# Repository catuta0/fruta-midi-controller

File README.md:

# FrutaMIDI — fruit MIDI controller

A USB MIDI controller with 12 capacitive pads (expandable to 24), in the style of the Playtron: touch a piece of fruit, a plant or a glass of water and a note comes out. It uses a Raspberry Pi Pico and an MPR121 sensor, costs about 25 € and works on **Windows and Mac** without drivers.

The MPR121 detects the touch, the Pico turns it into MIDI notes and the computer makes the sound. To change sounds, just change programs: the hardware stays the same.

**Online sampler:** <https://catuta0.github.io/fruta-midi-controller/> (open it in Edge or Chrome)

**Two ways to build it:**
- **Breadboard:** no soldering. This README.
- **Single-sided PCB, version 1.3**, for etching at home with the chemical method, with KiCad schematic, BOM and assembly guide: [`hardware/`](hardware/).
  The board has one copper layer, on the component side, and every part is surface-mounted (SMD), so the only holes are the 4 optional M3 mounting holes. All parts are sold by Mouser; one board costs about 13.84 EUR at Mouser Portugal prices of 2026-11-11, excluding shipping and tax (a calculation from list prices). What to know before you start (details in the [assembly guide](hardware/README.md)):
  - The **Pico is soldered flat** on its castellations and the **MPR121 module stands on its header pins**, both soldered onto surface pads, with no sockets. Only the Pico (SC0915) and the Pico 2 are supported on the PCB, not Pico W or Pico 2 W; with a Pico 2, check that the USB plug seats fully before soldering it. Flash the firmware before soldering the Pico. Replacing a failed one means desoldering it, which is harder than with sockets.
  - **USB end:** two small beads of 2-part epoxy along the long sides of the Pico, over pins 1–3 and 38–40; none on the USB end face or beyond the board edge, and check again after curing that the plug seats fully. Use a strain-relieved USB cable and do not lever on the plug.
  - **Electrode wires** are soldered onto pads and held with hot-melt glue. The **octave potentiometer** sits off the board on 3 wires: use one with an insulated shaft and a plastic knob. It has no bushing; the guide suggests mounting it on a small piece of perfboard behind the panel hole (not tried).
  - Module configuration: **JP1** is a surface solder bridge (ORIG or QT), set **before the module is fitted** because the module hides the ORIG label, and **J1** takes two short wire links.
  - **ESD:** each electrode has a 3.3 kΩ chip resistor. It is **not proven** that these standard resistors survive the project's ±4 kV static-discharge target; nothing has been tested (see [Safety](#design-notes) below).

> The firmware compiles without errors for all the boards listed, and the sampler was tested with simulated MIDI. <!-- EVIDENCE --> The complete build has not yet been tested on real hardware: if you run into problems, open an *issue*.

## Contents

- [Quick start (no programming)](#quick-start-no-programming)
- [PCB version](hardware/) (separate page)
- [Bill of materials](#bill-of-materials)
- [Wiring](#wiring)
- [Firmware](#firmware)
- [Sound](#sound)
- [Windows: what to know](#windows-what-to-know)
- [Design notes](#design-notes)
- [Step-by-step assembly](#step-by-step-assembly)
- [Troubleshooting](#troubleshooting)

## Quick start (no programming)

Works on Windows 10/11 and macOS; you do not need to install anything.

1. Build the hardware: see [Wiring](#wiring).
2. On the [Releases](https://github.com/catuta0/fruta-midi-controller/releases/latest) page, download the file for your board:

   | Board | Breadboard | FrutaMIDI PCB |
   | --- | --- | --- |
   | Raspberry Pi Pico | `FrutaMIDI-rpipico.uf2` | `FrutaMIDI-pcb-rpipico.uf2` |
   | Raspberry Pi Pico W | `FrutaMIDI-rpipicow.uf2` | `FrutaMIDI-pcb-rpipicow.uf2` (not supported on the v1.3 PCB, see below) |
   | Raspberry Pi Pico 2 | `FrutaMIDI-rpipico2.uf2` | `FrutaMIDI-pcb-rpipico2.uf2` |
   | Raspberry Pi Pico 2 W | `FrutaMIDI-rpipico2w.uf2` | `FrutaMIDI-pcb-rpipico2w.uf2` (not supported on the v1.3 PCB, see below) |

   The PCB uses different pins from the breadboard, so each build has its own file.

   The v1.3 PCB supports only the Raspberry Pi Pico (SC0915, recommended) and the Pico 2. Pico W and Pico 2 W are not supported on the PCB until their undersides have been checked against the keep-outs under the Pico ([assembly guide, A1](hardware/README.md#bill-of-materials)). On the breadboard all four boards work.

3. Hold the Pico's **BOOTSEL** button while you plug in the USB cable. A drive called **RPI-RP2** (Pico 2: **RP2350**) appears in Windows File Explorer or the Mac Finder.
4. Drag the `.uf2` onto that drive. The Pico restarts by itself and the drive disappears: this is normal.
5. Open the [online sampler](https://catuta0.github.io/fruta-midi-controller/) in Edge or Chrome. Click to enable sound and allow MIDI access.
6. Touch the fruit.

## Bill of materials

The essentials cost about 23–31 €. This total excludes the 14 recommended resistors (and, on the PCB, the JP1 solder bridge), because their price is not sourced. Prices are approximate and vary a lot between shops.

| Part | Qty | Purpose | Approx. price | Notes |
| --- | --- | --- | --- | --- |
| Raspberry Pi Pico or Pico 2 (**H** version, with headers already soldered) | 1 | Brain; shows up on the computer as a MIDI device | 5–7 € | Pico W and Pico 2 W also work |
| MPR121 breakout (Adafruit 1982 or CJMCU-121 clone) | 1 | 12 capacitive sensors | 3 € (clone) / 9 € (Adafruit) | Both run at 3.3 V, like the Pico |
| Micro-USB **data** cable | 1 | Connection to the computer | 3 € | Many cables are charge-only; if the Pico does not show up, it is the cable |
| 400-point breadboard | 1 | Solderless prototype | 3 € | |
| Male-to-male jumper wires | 10 | Breadboard connections | 2 € | |
| Leads with alligator clips on both ends | 12 | Connect each pad to an object | 5 € (pack of 10) | Buy 2 packs |
| Screw terminal strip, 12 ways | 1 | Sturdy connection point for the alligator clips | 2 € | 5 mm pitch is the easiest to tighten |
| Resistor 3.3 kΩ (3k3), axial | 12 | One in series with each electrode (ESD protection) | — | Recommended. The PCB (v1.3) uses 3.3 kΩ ±1 % surface-mount chip resistors in the 2512 size (YAGEO RC2512FK-073K3L); see the [assembly guide](hardware/README.md#bill-of-materials) |
| Resistor 4.7 kΩ (4k7), axial | 2 | I²C pull-ups, SDA and SCL to 3V3 | — | Recommended, because the firmware runs I²C at 400 kHz (Yageo MFR-12FTF52-4K7) |
| 6 mm push button | 1 | Change scale / recalibrate | 0.20 € | Optional, but very useful |
| 10 kΩ linear potentiometer (B10K) + knob | 1 | Change octave | 1.50 € | Optional |
| Second MPR121 | 1 | Pads 13 to 24 | 3–9 € | Optional |
| Project box ~100×60×25 mm or 3D print | 1 | Protect the electronics | 5 € | Optional |
| Perfboard + soldering iron | 1 | Permanent version | 3 € | After testing on the breadboard |
| Stainless steel nails or needles, copper tape, conductive paint | — | Electrodes | 5–10 € | Optional |

The firmware also compiles for the Arduino Pro Micro / Leonardo (ATmega32u4). In that case, use an Adafruit MPR121 (it accepts 5 V) or a 3.3 V Pro Micro: MPR121 clones only tolerate 3.3 V.

## Wiring

| Pico (GP) | Physical pin | Connects to | Function |
| --- | --- | --- | --- |
| 3V3(OUT) | 36 | MPR121 **VIN** (Adafruit) or **3.3V** (clone) | Sensor power |
| GND | 38 | MPR121 **GND** | Common ground |
| GP4 | 6 | MPR121 **SDA** | I²C data |
| GP5 | 7 | MPR121 **SCL** | I²C clock |
| — | — | MPR121 **IRQ** | Not connected: the firmware polls the sensor in a loop |
| — | — | MPR121 **ADDR** | Leave as is (0x5A); only changes on the 2nd sensor |
| GP15 | 20 | Button, leg 1 | Scale / recalibrate; the other leg goes to GND (pin 18) |
| GP26 / ADC0 | 31 | Potentiometer, middle pin | Octave (optional) |
| 3V3(OUT) | 36 | Potentiometer, one end | |
| AGND | 33 | Potentiometer, other end | |
| 3V3(OUT) | 36 | 4.7 kΩ resistor to SDA (GP4), and another 4.7 kΩ to SCL (GP5) | I²C pull-ups (recommended) |
| — | — | MPR121 **0–11** | Each pin through its own 3.3 kΩ resistor to the terminal strip, then one alligator clip per object |

Physical pins are counted from 1 to 40 with the USB facing up: pin 1 is the top-left corner, you go down the left side to 20 and back up the right side to 40.

**Second MPR121 (24 pads).** Connect it in parallel with the first, on the same 3V3, GND, SDA and SCL. To change its address to 0x5B, connect its **ADDR** pin to 3V3. On the clone, ADDR usually comes tied to GND by a trace or solder bridge that you must cut first. In the firmware, set `NUM_SENSORS = 2`; the `.uf2` files in Releases are for 1 sensor. With `NUM_SENSORS = 2`, an LED that keeps blinking fast means one of the two modules is not answering.

**Pro Micro / Leonardo.** SDA = pin 2, SCL = pin 3, button on pin 7, potentiometer on A0.

**Protection and pull-ups (recommended).** Put a 3.3 kΩ resistor in series between each MPR121 electrode pin (0–11) and its terminal, so the resistor sits between the sensor and anything you touch. Add two 4.7 kΩ pull-ups from 3V3 to SDA and to SCL: the firmware runs I²C at 400 kHz. These are the same values used on the [PCB](hardware/README.md#electrical-safety).

Keep the I²C wires short (under 10 cm). The leads to the fruit can be 20–50 cm, but kept apart from each other.

## Firmware

The code is in [`firmware/FrutaMIDI/FrutaMIDI.ino`](firmware/FrutaMIDI/FrutaMIDI.ino), with helper headers `fm_*.h` in the same folder. The scales are defined in [`fm_scales.h`](firmware/FrutaMIDI/fm_scales.h). You only need to compile it if you want to change the configuration; otherwise, use the `.uf2` files from the [Quick start](#quick-start-no-programming).

**What it does**

- Each touched pad sends Note On; when you let go, it sends Note Off for the same note, even if you have changed scale in the meantime.
- While you touch, it sends Polyphonic Aftertouch (0–127): more skin, or the hand closer, gives a higher value. When you let go, it sends aftertouch 0 before the Note Off, so the pressure never stays stuck. After an octave change two pads can play the same note: it sounds until the last of them is released.
- It has 6 scales. It starts in Drum Rack mode (notes 36–47, for triggering samples); the others are melodic.
- Button: a short press moves to the next scale and the LED blinks its number (1 Drum Rack · 2 Major pentatonic · 3 Minor pentatonic · 4 Major · 5 Natural minor · 6 Chromatic). Held for 0.8 s, it recalibrates.
- LED: 2 slow blinks at startup = sensor OK; blinking fast = MPR121 not found or lost during play (its notes are released and it retries about every 2 s); on = pad touched. The pads keep playing while the LED blinks; while a blink pattern runs, the LED shows the pattern instead of touches.

**Compiling (Arduino IDE 2, same on Windows and Mac)**

1. In the Arduino IDE preferences (*File → Preferences* on Windows, *Arduino IDE → Settings* on Mac), add this address to *Additional boards manager URLs*:
   `https://github.com/earlephilhower/arduino-pico/releases/download/global/package_rp2040_index.json`
2. In the *Boards Manager*, install **Raspberry Pi Pico/RP2040/RP2350** (Earle F. Philhower).
3. In the *Library Manager*, install **Adafruit MPR121** (accept the dependencies) and **MIDI Library** (FortySevenEffects). For the Pro Micro, install **MIDIUSB** instead of the MIDI Library.
4. Under *Tools*: *Board* → your board; *USB Stack* → **Adafruit TinyUSB**. Without this step it does not compile.
5. First upload: hold **BOOTSEL** while you plug in the USB and click *Upload*. Later uploads are automatic (on Windows, the Pico shows up as a COM port).

**Configuration** (at the top of the file)

| Constant | Default | Purpose |
| --- | --- | --- |
| `NUM_SENSORS` | 1 | 2 for 24 pads |
| `MIDI_CHANNEL` | 1 | MIDI channel (1–16) |
| `VELOCITY` | 100 | Fixed note velocity |
| `TOUCH_THRESHOLD` / `RELEASE_THRESHOLD` | 12 / 6 | Sensitivity: higher = less sensitive |
| `AUTOCONFIG` | true | Adjusts the charge current to the size of each object. Leave it on for fruit |
| `SEND_AFTERTOUCH` | true | Sends the "pressure" as Polyphonic Aftertouch |
| `USE_BUTTON` / `USE_POT` | true / false | Enables the button and the potentiometer |
| `SERIAL_DEBUG` | false | Prints each pad's "delta" to the Serial Monitor (115200) |
| `#define FRUTAMIDI_PCB` | off | Uncomment for the [PCB](hardware/): I²C on GP26/GP27, button on GP22, potentiometer on GP28 (and enabled) |

**Tuning the sensitivity:** set `SERIAL_DEBUG = true`, upload the firmware again and open the Serial Monitor. You see each pad's delta 4 times per second: close to 0 at rest, rising when you touch. `TOUCH_THRESHOLD` should sit roughly in the middle.

## Sound

FrutaMIDI does not make sound: it sends notes. Choose a program to turn them into sound.

**Browser sampler (included).** Open <https://catuta0.github.io/fruta-midi-controller/> in **Edge** (it comes with Windows) or Chrome. Safari does not have Web MIDI. The file is at [`docs/index.html`](docs/index.html) and also works when downloaded.

- 12 pads with synthesised drum sounds, mapped to notes 36–47 (the firmware's Drum Rack mode).
- Drag a wav, mp3 or ogg onto a pad to replace its sound.
- The **"learn"** button changes a pad's note: click it and touch the fruit.
- Notes without a pad (melodic scales) play on a synthesiser, and aftertouch opens the filter.
- Without hardware, the keys 1–4 / Q–R / A–F play the pads.

**Music programs**

| Program | System | Cost | How to use |
| --- | --- | --- | --- |
| [LMMS](https://lmms.io) | Windows, Mac, Linux | Free | *AudioFileProcessor* or *Kicker* instrument; enable MIDI input on the track |
| [Ableton Live](https://www.ableton.com/live/) | Windows, Mac | Paid, with trial version | Drum Rack (C1–B1 = notes 36–47); *Settings → Link, Tempo & MIDI* → enable **Track** on the FrutaMIDI input |
| [FL Studio](https://www.image-line.com) | Windows, Mac | Paid, with trial version | *FPC* for pads; enable FrutaMIDI in *Options → MIDI settings* |
| [Reaper](https://www.reaper.fm) | Windows, Mac | Free trial, cheap licence | Track with *ReaSamplOmatic5000*; MIDI record input → FrutaMIDI |
| GarageBand | Mac only | Free | *Software Instrument* track; recognises FrutaMIDI by itself |

For the classic "Playtron" effect (the sound lasts while your hand is on the fruit), use the DAW's sampler in *gate* or *hold* mode, not *one-shot*.

## Windows: what to know

- **No drivers.** Windows 10 and 11 recognise FrutaMIDI by themselves. To check, open *Device Manager*: it appears under *Sound, video and game controllers*.
- **One program at a time.** On Windows, a MIDI device can normally be opened by only one program at a time. If the DAW says FrutaMIDI is unavailable, close the sampler tab in the browser (and vice versa). The sampler warns you when the device is busy. The most recent versions of Windows 11 include *Windows MIDI Services*, which may lift this limitation.
- **Latency.** In the DAW, use an **ASIO** driver: your sound card's or, on a laptop without one, the free [ASIO4ALL](https://asio4all.org) or [FlexASIO](https://github.com/dechamps/FlexASIO). Set the buffer to 128 or 256 samples. With the standard driver (MME/shared WASAPI) the delay is noticeable.
- **Device name.** Windows keeps the name of the first device it saw with that USB identifier. If you have used the Pico with other firmware before, it may show up under another name; it works all the same.
- **Laptop on battery.** As on the Mac, sensitivity drops when the laptop is not plugged into the charger (see [Design notes](#design-notes)).

## Design notes

What matters most for the result is not the code: it is the objects, the cables and the ground connection. The MPR121 measures the capacitance of each electrode. When you touch it, your body, grounded through the floor and the computer, adds capacitance and the reading drops. The "delta" is that drop.

**Ground and computer**

- The circuit closes through you and the computer. A laptop on battery gives smaller, unstable deltas; plugged into the charger it usually improves.
- Makey Makey trick: an alligator clip connected to the Pico's GND on a wristband or on a "ground" object. Anyone touching it with the other hand gets a much stronger and more consistent touch.

**Which objects work**

- Good: fruit and vegetables with water in them (lemon, apple, cucumber, potato), thick-leaved plants, water in a glass, metal, copper tape, conductive paint, heavily shaded 6B pencil drawings, homemade salt dough.
- Bad: dry wood, plastic, glass, very dry fruit or fruit with a thick, dry skin.
- Objects must not touch each other or sit on a wet surface: that shorts pads together.
- For long events, hard vegetables (potato, carrot, apple) last for days; bananas and strawberries spoil quickly.

**Connecting to the object**

- An alligator clip on the skin alone works poorly. Push in a stainless steel nail or needle, or 1–2 cm of stripped wire, and clip onto that.
- Fruit acid oxidises copper within a few hours. Stainless steel lasts much longer.

**Cables**

- The cable itself is part of the electrode: touching the wire also triggers the note, and long cables pick up noise.
- Use up to 50 cm per cable, kept apart from each other. Do not use flat multi-conductor cable or tied bundles: touching one wire triggers its neighbour (crosstalk).

**Calibration and sensitivity**

- At startup, the MPR121 measures each electrode's "baseline" and, with `AUTOCONFIG`, adjusts the charge current to the size of the object. Connect the fruit before the USB, or hold the button for 0.8 s after swapping objects, without touching anything.
- Ghost notes: raise the thresholds to 20 / 10. No response: lower them to 8 / 4. Measure first with `SERIAL_DEBUG`.
- Very large objects (a whole watermelon, a pot of damp soil) can fall outside the sensor's range: the pad stays on all the time or never turns on. Use a smaller object or a piece of it.

**Enclosure and permanent version**

- After testing on the breadboard, solder everything onto a perfboard. Put the Pico in a female header so you can remove it.
- Terminal strip or 4 mm binding posts on the lid, numbered 0–11, and holes for the USB and the button.
- Use a plastic or wooden box: metal near the electrodes takes away sensitivity.

**Safety.** FrutaMIDI is USB-powered with 3.3 V logic. On the [PCB (v1.3)](hardware/README.md#electrical-safety), each electrode has a 3.3 kΩ series chip resistor (2512 size) and sits next to a spark gap to GND. The protection target is an IEC 61000-4-2 contact discharge of ±4 kV, and that target is itself an assumption. Whether the resistors survive it is **not proven**: they are standard parts with no published surge rating, a choice accepted to keep the board cheap. If the planned physical ESD test shows damage (a resistor whose value shifts, a channel that stops detecting touch, or a spark across a resistor), the fallback is a board revision with clamp diodes. Nothing has been tested, and the board does not cover 8 kV. The PCB has not been evaluated beyond that. Use an insulated-shaft potentiometer with a plastic knob on the PCB: a metal shaft is not protected. The breadboard build has no ESD protection on the electrodes beyond the MPR121's internal protection (HBM ±2 kV): the module connects its electrode pins straight to its header. The recommended 3.3 kΩ series resistors (see [Wiring](#wiring)) have the same value as the PCB's protection, but a small resistor is not rated for the ESD pulse, and no resistor has been evaluated in a breadboard layout. Neither build has been evaluated for touching while connected to mains-powered equipment. <!-- EVIDENCE --> Never connect the electrodes to anything plugged into mains power.

## Step-by-step assembly

Test each step before moving on: when something fails, you know straight away where the problem is.

1. **Pico alone.** Upload the firmware with only the Pico connected. The LED should blink fast, because there is no sensor yet, and FrutaMIDI already shows up in the sampler.
2. **Sensor.** With the USB unplugged, place the Pico and the MPR121 on the breadboard and connect the 4 wires: 3V3, GND, SDA and SCL, plus the two 4.7 kΩ pull-ups (3V3 to SDA, 3V3 to SCL). When you plug in the USB: 2 slow blinks, then the LED off.
3. **First touch.** Touch pin 0 of the MPR121 directly with your finger. The LED lights up and the sampler shows "Note On C1 (36)".
4. **First fruit.** One alligator lead from pin 0 to a nail pushed into a lemon. Recalibrate (0.8 s on the button, or unplug and replug the USB) without touching anything, then touch the lemon.
5. **Tune.** If there are ghost notes or missed touches, adjust the thresholds (see [Design notes](#design-notes)).
6. **All 12 pads.** Add the terminal strip, with a 3.3 kΩ resistor between each MPR121 pin and its terminal, and the rest of the fruit, recalibrate, and test pad by pad in the sampler.
7. **Controls.** Add the button (GP15 ↔ GND) and, if you like, the potentiometer with `USE_POT = true`.
8. **Final version.** Move to the perfboard and the enclosure.

## Troubleshooting

| Symptom | Likely cause | What to do |
| --- | --- | --- |
| Compile error mentioning `Adafruit_TinyUSB` or `usbMidi` | Wrong USB Stack | *Tools → USB Stack → Adafruit TinyUSB* |
| The Pico does not show up at all | Charge-only cable | Change the cable; test with BOOTSEL held (the RPI-RP2 drive should appear) |
| LED keeps blinking fast | MPR121 not responding on I²C | Check 3V3/GND and that SDA→GP4 and SCL→GP5 are not swapped; on the 2nd sensor, check ADDR |
| Windows: the DAW does not see FrutaMIDI, or the sampler says "ocupado" (busy) | Another program has the device open | Close the other program (or the sampler tab) and reopen |
| It shows up, but the DAW does not play | MIDI input disabled or track not armed | Enable the FrutaMIDI input in the DAW's MIDI settings and arm the track |
| Windows: the sound arrives late | Audio driver without ASIO | Use ASIO (ASIO4ALL or FlexASIO) with a buffer of 128–256 |
| A pad is always on | It calibrated with a hand on the object, or the object is too large | Recalibrate without touching; use a smaller object; raise the threshold |
| Touching one pad triggers its neighbour | Wires together or objects touching | Move the cables apart and separate the objects; dry the table |
| Ghost notes when the hand gets close | Low threshold or long cables | Raise to 20 / 10; shorten the cables |
| Sensitivity changes over the day | Fruit drying out, laptop on battery | Recalibrate; plug in the charger; use the ground-wire trick |
| A note gets stuck in the DAW | You unplugged the USB with a hand on the object | Touch and release the same pad again: the Note Off frees the note |
| The sampler says there is no Web MIDI | Safari, or an old browser | Use Edge or Chrome |

## Licence

[MIT](LICENSE): you are free to use, modify and share it.

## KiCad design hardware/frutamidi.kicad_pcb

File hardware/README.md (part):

# FrutaMIDI: single-sided SMD PCB (version 1.3)

A 100 × 70 mm board with copper on the **component side only**, designed for chemical etching at home (toner transfer or photosensitive board). Everything is surface-mounted, so the only holes are the 4 M3 mounting holes. The board carries a Raspberry Pi Pico soldered on its castellations, an Adafruit MPR121 module (1982) standing on its header pins, 14 solder-wire pads for the electrodes and GND, a button, three wire pads for an off-board potentiometer, a 3.3 kΩ series resistor on each electrode, two I²C pull-up resistors and two 220 Ω I²C series resistors.

> **Status:** the schematic passes ERC and the PCB passes DRC, both with no violations, and the PCB matches the schematic. <!-- EVIDENCE --> The board has not been fabricated, soldered or tested. Hand-soldering the Pico and the module header joints has not been tried. ERC and DRC passing does not validate the hardware. If you make one, open an *issue* with the result.

## Contents

- [Files](#files)
- [Bill of materials](#bill-of-materials)
- [Design rules for home etching](#design-rules-for-home-etching)
- [1. Print](#1-print)
- [2. Transfer and etch](#2-transfer-and-etch)
- [3. Drill](#3-drill)
- [4. Solder](#4-solder)
- [5. Module configuration: JP1 and two wires](#5-module-configuration-jp1-and-two-wires)
- [6. Test before soldering the Pico and the module](#6-test-before-soldering-the-pico-and-the-module)
- [7. Firmware and first power-up](#7-firmware-and-first-power-up)
- [Common problems](#common-problems)
- [Electrical safety](#electrical-safety)
- [Modifying the board](#modifying-the-board)

## Files

| File | Purpose |
| --- | --- |
| [`fabrication/1-copper-for-transfer.pdf`](fabrication/1-copper-for-transfer.pdf) | **What you print** for toner or positive photosensitive board. 1:1 scale, already mirrored for transfer onto the component-side copper |
| [`fabrication/1b-copper-negative.pdf`](fabrication/1b-copper-negative.pdf) | The same in negative, only for dry film / negative resist |
| [`fabrication/2-assembly-map.pdf`](fabrication/2-assembly-map.pdf) | Where each component goes, with references and pin 1. There is no silkscreen on the board: keep this page at the bench |
| [`fabrication/frutamidi-schematic.pdf`](fabrication/frutamidi-schematic.pdf) | Schematic |
| [`fabrication/gerbers/`](fabrication/gerbers/) | Gerbers + Excellon drill files, if you prefer to order the board |
| [`fabrication/bom-kicad.csv`](fabrication/bom-kicad.csv) | BOM exported from KiCad, with manufacturer, part number and Mouser number columns |
| `frutamidi.kicad_pro` / `.kicad_sch` / `.kicad_pcb` | KiCad 10 project, with its own libraries (`FrutaMIDI.kicad_sym`, `FrutaMIDI.pretty/`) |
| [`scripts/`](scripts/) | Schematic and PCB generators, and `build_all.sh` (regenerates, checks and exports) |

## Bill of materials

### Components

All parts below are sold by Mouser. One board costs about 13.84 EUR at Mouser Portugal prices of 2026-11-11 (12 resistors at the 10+ price, everything else at the single-unit price), excluding shipping and tax.

| Ref. | Part | Qty | Notes |
| --- | --- | --- | --- |
| A1 | Raspberry Pi Pico, Raspberry Pi **SC0915** (Mouser 358-SC0915). The **Pico 2** also fits. **Pico W and Pico 2 W are not supported on this board** until their underside has been checked against the keep-outs. The castellated pads must be free, so **no** H version with headers fitted | 1 | Surface-soldered on its castellated edge pads. There are no sockets: a failed Pico must be desoldered from the surface. The keep-outs under it cover the test points and USB pads of both the Pico and the Pico 2, including the Pico 2's TP7 (1.1 V core supply) |
| A2 | Adafruit MPR121 12-key capacitive touch breakout, Adafruit **1982** (Mouser 485-1982) | 1 | Original or STEMMA QT: both work (section 5). Use the male headers supplied with it |
| R1–R12 | Thick-film chip resistor 3.3 kΩ ±1 %, 1 W, 2512, YAGEO **RC2512FK-073K3L** (Mouser 603-RC2512FK-073K3L) | 12 | One in series with each electrode. **Stock is tight:** Mouser showed 13 in stock on 2026-11-11, next delivery May 2027. Any 3.3 kΩ ±1 % 2512 chip with a body 6.35 × 3.1 mm fits the same pads. **Alternative in stock:** Vishay **CRCW25123K30FKEG** (Mouser 71-CRCW25123K30FKEG, 3.3 kΩ 1 %, 2512): Mouser showed 4,500 in stock on 2026-11-11, 0.424 EUR each at 10+ (about 5.09 EUR for 12, against 1.31 EUR for the YAGEO part). Its datasheet has not been checked for this board: confirm that the body is the standard 6.35 × 3.1 mm 2512 size before ordering. Neither part has a published surge rating, see [Electrical safety](#electrical-safety) |
| R13, R14 | Resistor 4.7 kΩ 1 %, 1206, YAGEO **RC1206FR-074K7L** (Mouser 603-RC1206FR-074K7L) | 2 | I²C pull-ups (SCL, SDA) |
| R15, R16 | Resistor 220 Ω 1 %, 1206, YAGEO **RC1206FR-07220RL** (Mouser 603-RC1206FR-07220RL) | 2 | In series in SCL (R15) and SDA (R16), on the Pico side; they limit the current if a configuration wire goes to the wrong pad |
| C1 | Ceramic capacitor 100 nF 50 V X7R, 1206, Samsung **CL31B104KBCNNNC** (Mouser 187-CL31B104KBCNNNC) | 1 | Potentiometer wiper to AGND, near the Pico |
| SW1 | Tactile switch **B3S-1000** (6 × 6 mm, SMD, height 4.3 mm; Mouser 653-B3S-1000) | 1 | Mouser lists the maker as **Aratas**; its maker page says "ARATAS, formerly Omron Components", so this is the genuine Omron B3S-1000 (checked 2026-11-11) |
| RV1 | 10 kΩ linear potentiometer, Bourns **PTV09A-4015F-B103** (Mouser 652-PTV09A-4015FB103; 9 mm, insulated flatted shaft 6 mm, 15 mm long, no bushing, PC pins), off-board, connected by 3 wires | 1 | Mount it in your enclosure and solder the 3 wires to its pins. See [Electrical safety](#electrical-safety): keep the insulated shaft and use a plastic knob. If the octave goes down when you turn clockwise, swap the two outer wires |
| — | Knob for RV1, Same Sky **SPK-016A** (Mouser 179-SPK-016A; ABS, 11 mm, for 6 mm shafts) | 1 | Whether its bore grips the flatted shaft is not confirmed; check the fit, or use any plastic knob for a 6 mm flatted (D) shaft |
| J1, J2, J3, JP1 | Etched copper pads only (no part): J1 configuration-wire pads, J2 electrode wire pads, J3 S1–S7 pads, JP1 solder bridge | — | Not in `bom-kicad.csv`. JP1 is bridged with a short tinned wire off-cut, see section 5. The RV1 knob is also not in `bom-kicad.csv` (it has no schematic symbol); this table is the full list |
| — | Thin insulated solid wire (from network cable, for example) | ~10 cm | The 2 configuration wires (SDA, SCL) |
| — | Electrode wire, insulated, 0.25–0.5 mm² | 12 + GND | Soldered to the J2 pads, then strain-relieved with hot-melt glue |
| — | Hot-melt glue, 2-part epoxy | — | Hot-melt on each J2 wire and RV1 wire; epoxy at the Pico USB end |
| H1–H4 | M3 screws + spacers, **nylon** preferred | 4 | Optional; see the mounting note in section 4. Nylon keeps loose metal away from the electrode resistors |
| — | Micro-USB **data** cable, strain-relieved or supported | 1 | The USB connector is held only by the castellation solder joints and the epoxy bead. Do not lever on the plug |

### Fabrication materials

| Part | Qty | Notes |
| --- | --- | --- |
| **Single-sided** copper board, FR4 or FR2, 100 × 70 mm (35 µm) | 1 | Or cut from a larger one |
| **Toner:** laser printer + transfer paper (or glossy magazine paper) + clothes iron | — | Inkjet ink does not work |
| **Photographic:** positive pre-sensitised board + transparency film + UV lamp + developer (sodium hydroxide) | — | Alternative to toner |
| Ferric chloride (or sodium persulfate) | ~0.5 L | See the safety note in section 2 |
| Plastic container, nitrile gloves, goggles | — | Nothing metal |
| Acetone or thinner, fine steel wool, isopropyl alcohol | — | Cleaning |
| Fine permanent marker | 1 | Touching up toner gaps |
| Drill bit of **3.2 mm** | 1 | For the 4 mounting holes, which are the only holes on the board |
| Soldering iron with a fine chisel tip, flux, flux-core solder (0.5–0.8 mm), tweezers, multimeter, polyimide tape (optional) | — | |

## Design rules for home etching

| Rule | Value |
| --- | --- |
| Copper layers | One layer, on the component side (top). SMD only |
| Holes | Only the 4 M3 mounting holes (not plated) |
| Track width | 1.0 mm (signals) and 1.2 mm (GND, 3V3); 0.8 mm on the short S-row stubs |
| Minimum clearance | 0.6 mm (project rule); 0.5 mm is the absolute minimum accepted by DRC |
| Vias and bridges | No vias, no copper pour. Only the JP1 solder bridge and the 2 module configuration wires |
| Pads | Pico 1.6 × 4.2 mm (all 40 etched, 0.94 mm gap), module 1.8 × 4.2 mm (13-pin row) and 1.8 × 5.5 mm (7-pin row, joined to the S1–S7 pads), 0.74 mm gap, J2 3.0 × 4.5 mm, RV1 3.0 mm, JP1 1.94 × 2.4 mm on a 3.81 mm pitch (1.87 mm between pads), 1206 parts 1.8 × 1.8–1.9 mm. Every hand-soldered pad reaches at least 1.0 mm beyond the part body (or the module outline), so the iron touches the pad outside the part |
| Keep-out under the Pico | No bare copper under the Pico's exposed test points and USB shell pads, nor under its 3 SWD pads: TP6 is BOOTSEL, so a short there means a Pico that always boots to mass storage |
| Ground plane | None, on purpose: copper around the electrode tracks takes away sensitivity |

## 1. Print

1. Open [`1-copper-for-transfer.pdf`](fabrication/1-copper-for-transfer.pdf) and print at **actual size / 100 %**, without "fit to page".
2. Measure the printed outline: it must be **100 × 70 mm**. If it is not, the printer scale is wrong.
3. Check that the text **"FrutaMIDI v1.3" appears reversed (mirrored) on the paper**, and that the Pico pads appear on the **right** of the page. That is intended: transferred onto the copper, the text reads correctly when you look at the copper with the components on it.
4. For toner: laser printer, maximum density, transfer paper. For photosensitive board: transparency film, preferably two copies stacked so it is fully opaque.

## 2. Transfer and etch

**Preparing the board:** cut the blank **oversize**, about 110 × 80 mm, and rub the copper with steel wool until it shines. The outline is printed with the tracks and etched as a thin copper line: after etching (and before soldering), trim the board to the **outside of that etched line** with a saw or shears and file the edges. The Pico's USB end lies on the top edge, with its connector sticking out about 1.2 mm, so do not cut inside the line at that edge. Clean it with alcohol and do not touch it with your fingers again.

**Toner**

1. Place the paper with the ink facing the copper and hold it with tape.
2. Iron on maximum, no steam, 3–5 minutes with pressure, going well over the corners.
3. Let it cool, soak in warm water for 5–10 minutes and remove the paper by rubbing with your finger.
4. Touch up broken tracks or pads with holes using the permanent marker.

**Positive photosensitive**

1. Place the transparency with the ink facing the resist.
2. Expose to UV light as the manufacturer specifies (usually 1–3 minutes), develop, rinse in water and check that the tracks are sharp.

**Etching**

- Ferric chloride at 40–50 °C (water bath), agitating: 10–20 minutes. Take the board out when all the copper between the tracks has gone.
- Rinse with water, remove the toner/resist with acetone, and check against the light that there are no bridges between tracks, especially between the Pico pads, in the electrode fan-out and at JP1.
- **Keep the 1.4 mm gap between each electrode pad and the GND track along the bottom edge clean and open:** it is an intentional spark gap (see [Electrical safety](#electrical-safety)).

**Safety:** wear gloves and goggles, in a ventilated place. Ferric chloride stains everything permanently and is corrosive. Do not pour the used solution down the drain: it contains dissolved copper, so take it to a recycling/waste collection centre. If you use hydrochloric acid with hydrogen peroxide, always mix it in small quantities and outdoors, because it releases toxic gases.

## 3. Drill

Drill only the 4 mounting holes, **3.2 mm**, at H1–H4 (see the assembly map). They are optional: without them the board can be fixed with adhesive feet. There are no other holes.

If you like, tin the bare copper with the iron or apply protective lacquer after etching, but keep lacquer off every pad you are going to solder.

## 4. Solder

Use the [assembly map](fabrication/2-assembly-map.pdf). Work from the lowest parts to the tallest. **Clean flux from around R1–R12 afterwards with isopropyl alcohol:** residue on the bare FR-4 between the two ends of each resistor shortens the surface path that the 4 kV estimate relies on.

1. **R13–R16 (1206) and C1 (1206).** Tin one pad, place the part with tweezers, solder that end, then the other. C1 is not polarised.
2. **R1–R12 (2512, 3.3 kΩ).** One per electrode, in one row between the module and J2. Keep solder off the 5.0 mm gap between the two pads and do not let any wire or solder cross it.
3. **Button SW1** (B3S-1000). Align all four legs on their pads and solder them all.
4. **[Run section 6 now](#6-test-before-soldering-the-pico-and-the-module)**, before the Pico and the module go on. After that you cannot get under them.
5. **Pico (A1).** Flash the firmware first, while the Pico is still loose (section 7). Check that no bare copper shows under the test-point areas marked on the assembly map. Lay the Pico on its pads with the USB end at the top edge of the board: the end of the Pico is 0.1 mm inside the board edge and the USB connector sticks out about 1.2 mm beyond it. **Before soldering, plug the cable in** with the Pico held in place: the plug must go fully home without touching the board edge; if it does not, file the board edge back to the etched outline. Press the Pico down at each corner: it must **not rock**. Solder left at the USB connector pins on the Pico's underside can hold it up; if it rocks, remove that solder with braid first. Then align the castellations over the pads, hold the board flat, tack two opposite corner pads, check alignment, then solder all 40 pads from the outer edge of each castellation. All 40 are anchors, even those without a track.
6. **Epoxy at the USB end.** After soldering and after a first USB check that the Pico still starts (the fast LED blink without the module is expected), apply a small bead of 2-part epoxy along the end of the Pico at the USB connector, joining the module edge to the board, without touching the USB opening. Use a strain-relieved cable: a sharp pull on the plug can peel the end pads.
7. **Module (A2).** Fit the supplied male header to the module from below, short pins up through the module, with the plastic strip pushed **up against the underside** of the module, and solder the pins on the top of the module. Cut the long pins below the strip to **3.0 mm** (measure from the strip; cut all 20 to the same length, a strip of card 3 mm thick helps). Stand the module on its 20 pads (13-pin row towards J2, as on the assembly map): each pin stands near the inner end of its pad, and the pad runs about 1.7 mm out beyond the edge of the module. Solder each pin from **outside the module**: put the iron on the outer part of the pad, feed solder where the pad meets the pin, and check that a fillet climbs the pin. The module must sit level on both rows; tack one pin at each end of each row first. The underside of the module ends up about 5.5 mm above the board (3.0 mm pin + 2.5 mm strip, not measured), which keeps its copper and vias well off the bare tracks; the top of the module board is about 7.1 mm above the copper, plus the parts on it (the 1.6 mm module thickness is assumed, not measured).
8. **JP1 and the 2 configuration wires** (section 5).
9. **RV1 wires.** Three insulated wires to pads 1 (3V3), 2 (wiper), 3 (AGND) to your off-board pot. Add a small bead of hot-melt over the wires, on the pads, for strain relief. Keep the wires short.
10. **Electrode and GND wires (J2).** Strip about **3–4 mm** of each wire and tin it. Lay it on the upper half of its pad so that the wire leaves the pad **upwards, towards the resistors, away from the board edge**, and solder it there, leaving the part of the pad next to the board edge clean. A wire led out over the bottom edge would cross the spark gap: lead the wires sideways off the board only after the hot-melt, above the pads. Add a bead of hot-melt over the wire and the upper pad. **Keep the glue away from the 1.4 mm gap at the bottom of the pad:** the spark gap must stay open air.

**Optional: silicone over R1–R12.** It is not needed to meet the 3.5 mm gap rule, which the resistor terminations already meet. If you want an extra cover against dust and moisture, apply it only after cleaning and after the tests in section 6, as one continuous bead without bubbles or voids over each resistor and its two pads. Use only a **neutral-cure, electronics-grade** silicone, never an acetic-cure (vinegar-smelling) bathroom silicone, which corrodes copper and solder. No particular product has been checked for this board.

**Mounting (M3).** The four holes are at H1 (5.0, 65.0), H2 (96.0, 4.0), H3 (96.5, 58.0) and H4 (29.8, 4.0) mm from the top-left board corner, as seen on the assembly map; the outer circle drawn around each hole is the 7 mm area kept free of copper. H4 is the screw closest to the USB end of the Pico: fit it if you fit any, because it stops the board bending when a cable is pulled. It does not make the Pico solder joints stronger, so the epoxy bead and a strain-relieved cable stay necessary.

Use M3 screws no wider than 5.6 mm under the head, with a washer of at most 7 mm. **Nylon screw and nylon washer preferred**, above all at H3, which is nearest the electrode resistors (and at H4, where a 7 mm metal washer would be only 0.6 mm from the Pico pads and the 3V3 track). If you use metal hardware, check after tightening that no washer touches copper or a part.

**Rework:** the Pico and the module are soldered flat, so a failed one has to be desoldered from the surface. Use plenty of flux and hot air or a wide iron tip on one side at a time.

## 5. Module configuration: JP1 and two wires

The Adafruit 1982 exists in two versions, with the 7 power/I²C pins in a different order. That is why the board does not connect them directly. Above the 7 module pins there are 7 surface pads **S1–S7** (J3), each one directly above a module pin. You configure the board for your module in two steps.

**Step 1: power (JP1).** JP1 is a 3-pad solder bridge standing upright to the right of the module, with **QT** etched above its top pad (pad 3) and **ORIG** etched to its left, beside the gap between the centre pad and the bottom pad. ORIG means the bottom pad (pad 1), where the S1 track comes in from the left; QT means the top pad (pad 3), where the S7 track comes in. The centre pad is 3V3. Bridge it to **one** side with a short tinned wire off-cut soldered flat across the two pads, or with solder. The pads are 3.81 mm apart (1.87 mm of bare board between them), so that a single blob cannot easily join all three; a solder-only bridge needs generous solder, the wire off-cut is easier:

- **ORIG** (pad 1 → S1): original version, 3V3 goes to **VIN**.
- **QT** (pad 3 → S7): STEMMA QT version, 3V3 goes to **VCC**.

**Step 2: I²C (two wires).** J1 (right of JP1) has 2 surface pads, **SCL on the left and SDA on the right**. Connect:

- J1 **SDA** → the S pad above the module's **SDA** pin;
- J1 **SCL** → the S pad above the module's **SCL** pin.

To confirm, read the letters printed on the module next to the 7-pin row, and check this table:

| Version | How to recognise it | JP1 | SDA → | SCL → |
| --- | --- | --- | --- | --- |
| Original | No small white connectors | **ORIG** | **S5** | **S6** |
| STEMMA QT (current) | Two small white 4-pin connectors (STEMMA QT / Qwiic) | **QT** | **S3** | **S4** |

Use insulated solid wire, run flat on the board and as short as the route allows (about 25–35 mm each). Solder each end flat on its surface pad, then add a small dab of hot-melt so the wire is not held by the joint alone. The module's GND needs no wire: it comes in through the electrode row and is the same in both versions.

> **A wrong JP1 position can damage the sensor.** ORIG on a STEMMA QT module puts 3V3 on the module's ADDR pin; QT on an original module puts it on IRQ. The MPR121 chip is then unpowered, so 3V3 on that pin is above its absolute maximum rating (VDD + 0.3 V), and it can back-feed the module through its 10 kΩ pull-ups. There is no direct short to GND, but the module is not supplied correctly, the sensor does not respond and the Pico LED blinks fast. Check JP1 against the table above **before** powering. Never bridge all three pads.

## 6. Test before soldering the Pico and the module

With the multimeter, after step 3 of section 4 and **before the Pico and the module go on**, because you cannot reach underneath them afterwards:

- [ ] Continuity between the **JP1 centre pad** (3V3) and a **GND** pad of J2: it must **not** beep.
- [ ] Resistance between each electrode pad of J2 and the matching pin pad of the 1×13 module row: about **3.3 kΩ** (3267–3333 Ω, plus your meter's error). It does not beep in continuity mode.
- [ ] Continuity between neighbouring J2 pads (0–1, 1–2, …): it does **not** beep.
- [ ] Continuity between the two GND pads at the ends of J2: it beeps.
- [ ] Resistance between the pads of pin 31 and pin 32 of the Pico footprint and the J1 SDA / SCL pads (through R16 / R15): about **220 Ω**.
- [ ] Inspect with a magnifier: no bridges between the Pico pads, no copper left in the keep-out areas marked on the assembly map.

Then the final checks, after the Pico and module are soldered and JP1 is bridged, with the USB still unplugged:

- [ ] Continuity between the JP1 centre pad and the S pad for your version (S1 for ORIG, S7 for QT): it beeps. The other side (S7 or S1) must **not** beep.
- [ ] Pico pads **36** (3V3), **39** (VSYS) and **40** (VBUS) to any GND pad (for example Pico pad 38): none of them may beep. Pads 39 and 40 have no track on this board but lie 0.94 mm from the GND pad 38, so a solder bridge there shorts the USB supply. (Through the Pico's own circuit a meter may show a resistance or a diode drop between them; it must not show a short.)
- [ ] The button pad next to the Pico (the upper left SW1 pad, BTN) to Pico pad **30** (RUN): it must **not** beep. Pad 30 is unused on this board but sits 1.07 mm from that button pad; a bridge there would reset the Pico when the button is pressed.

## 7. Firmware and first power-up

The board uses different pins from the breadboard, so it needs the **PCB version** of the firmware:

| Board | File (in [Releases](https://github.com/catuta0/fruta-midi-controller/releases/latest)) |
| --- | --- |
| Raspberry Pi Pico | `FrutaMIDI-pcb-rpipico.uf2` |
| Raspberry Pi Pico W (breadboard only: not supported on this PCB, see A1 in the parts list) | `FrutaMIDI-pcb-rpipicow.uf2` |
| Raspberry Pi Pico 2 | `FrutaMIDI-pcb-rpipico2.uf2` |
| Raspberry Pi Pico 2 W (breadboard only: not supported on this PCB, see A1 in the parts list) | `FrutaMIDI-pcb-rpipico2w.uf2` |

1. With the Pico **off the board**, hold BOOTSEL, plug in the USB and drag the `.uf2` onto the RPI-RP2 drive (on the Pico 2: RP2350).
2. Unplug the USB and solder the Pico, with its **USB end at the top edge** of the board and pin 1 as marked on the assembly map.
3. Solder the module with the **13-pin row facing J2**: the module's lettering ends up upside down, and that is intended.
4. Plug in the USB. The Pico LED should give 2 slow blinks (sensor found) and then light up whenever you touch an electrode wire.
5. Open the [online sampler](https://catuta0.github.io/fruta-midi-controller/), touch the wire on E0 with your finger and the kick drum should play.

Firmware can also be updated with the Pico soldered, because the BOOTSEL button is on the top of the Pico.

If you compile it yourself, uncomment `#define FRUTAMIDI_PCB` at the start of [`FrutaMIDI.ino`](../firmware/FrutaMIDI/FrutaMIDI.ino). This definition moves I²C to GP26/GP27 (`Wire1`), the button to GP22 and the potentiometer to GP28, and enables the potentiometer.

| Signal | Pico pin | GP |
| --- | --- | --- |
| SDA (I²C1) | 31 | GP26 |
| SCL (I²C1) | 32 | GP27 |
| Button | 29 | GP22 |
| Potentiometer | 34 | GP28 / ADC2 |
| 3V3 | 36 | — |
| AGND | 33 | — |
| GND | 3, 8, 13, 18, 23, 28, 38 | — |

## Common problems

| Symptom | Likely cause | What to do |
| --- | --- | --- |
| Pico LED blinks fast | Sensor not responding | Check that JP1 is bridged to the side for your version and that the 2 wires go to the right S pads; check that you uploaded the **pcb** `.uf2` |
| Nothing happens when plugged in, Pico in BOOTSEL mode all the time | Copper or solder touching the Pico's test points under the Pico | Inspect the keep-out under the Pico; you may need to desolder |
| Nothing happens when plugged in | Bad Pico castellation joint, or charge-only cable | Re-flow the Pico joints; change the cable |
| One electrode is always playing | Copper or solder bridge between tracks | Look with a magnifier in the electrode fan-out and the resistor row; cut with a craft knife |
| Two electrodes play together | Short between neighbouring tracks | Same procedure |
| One electrode never plays | Resistor of that electrode not soldered, or broken track | Measure about 3.3 kΩ from the wire to the module pad (section 6); re-solder |
| The potentiometer does not change the octave | Breadboard firmware, or a broken RV1 wire | Upload the **pcb** `.uf2`; check the three wires |
| The octave jumps by itself | RV1 wire badly soldered | Re-solder and strain-relieve the wires |

Sensitivity problems (fruit, cables, ground) are the same as on the breadboard: see the [design notes in the main README](../README.md#design-notes).

## Electrical safety

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
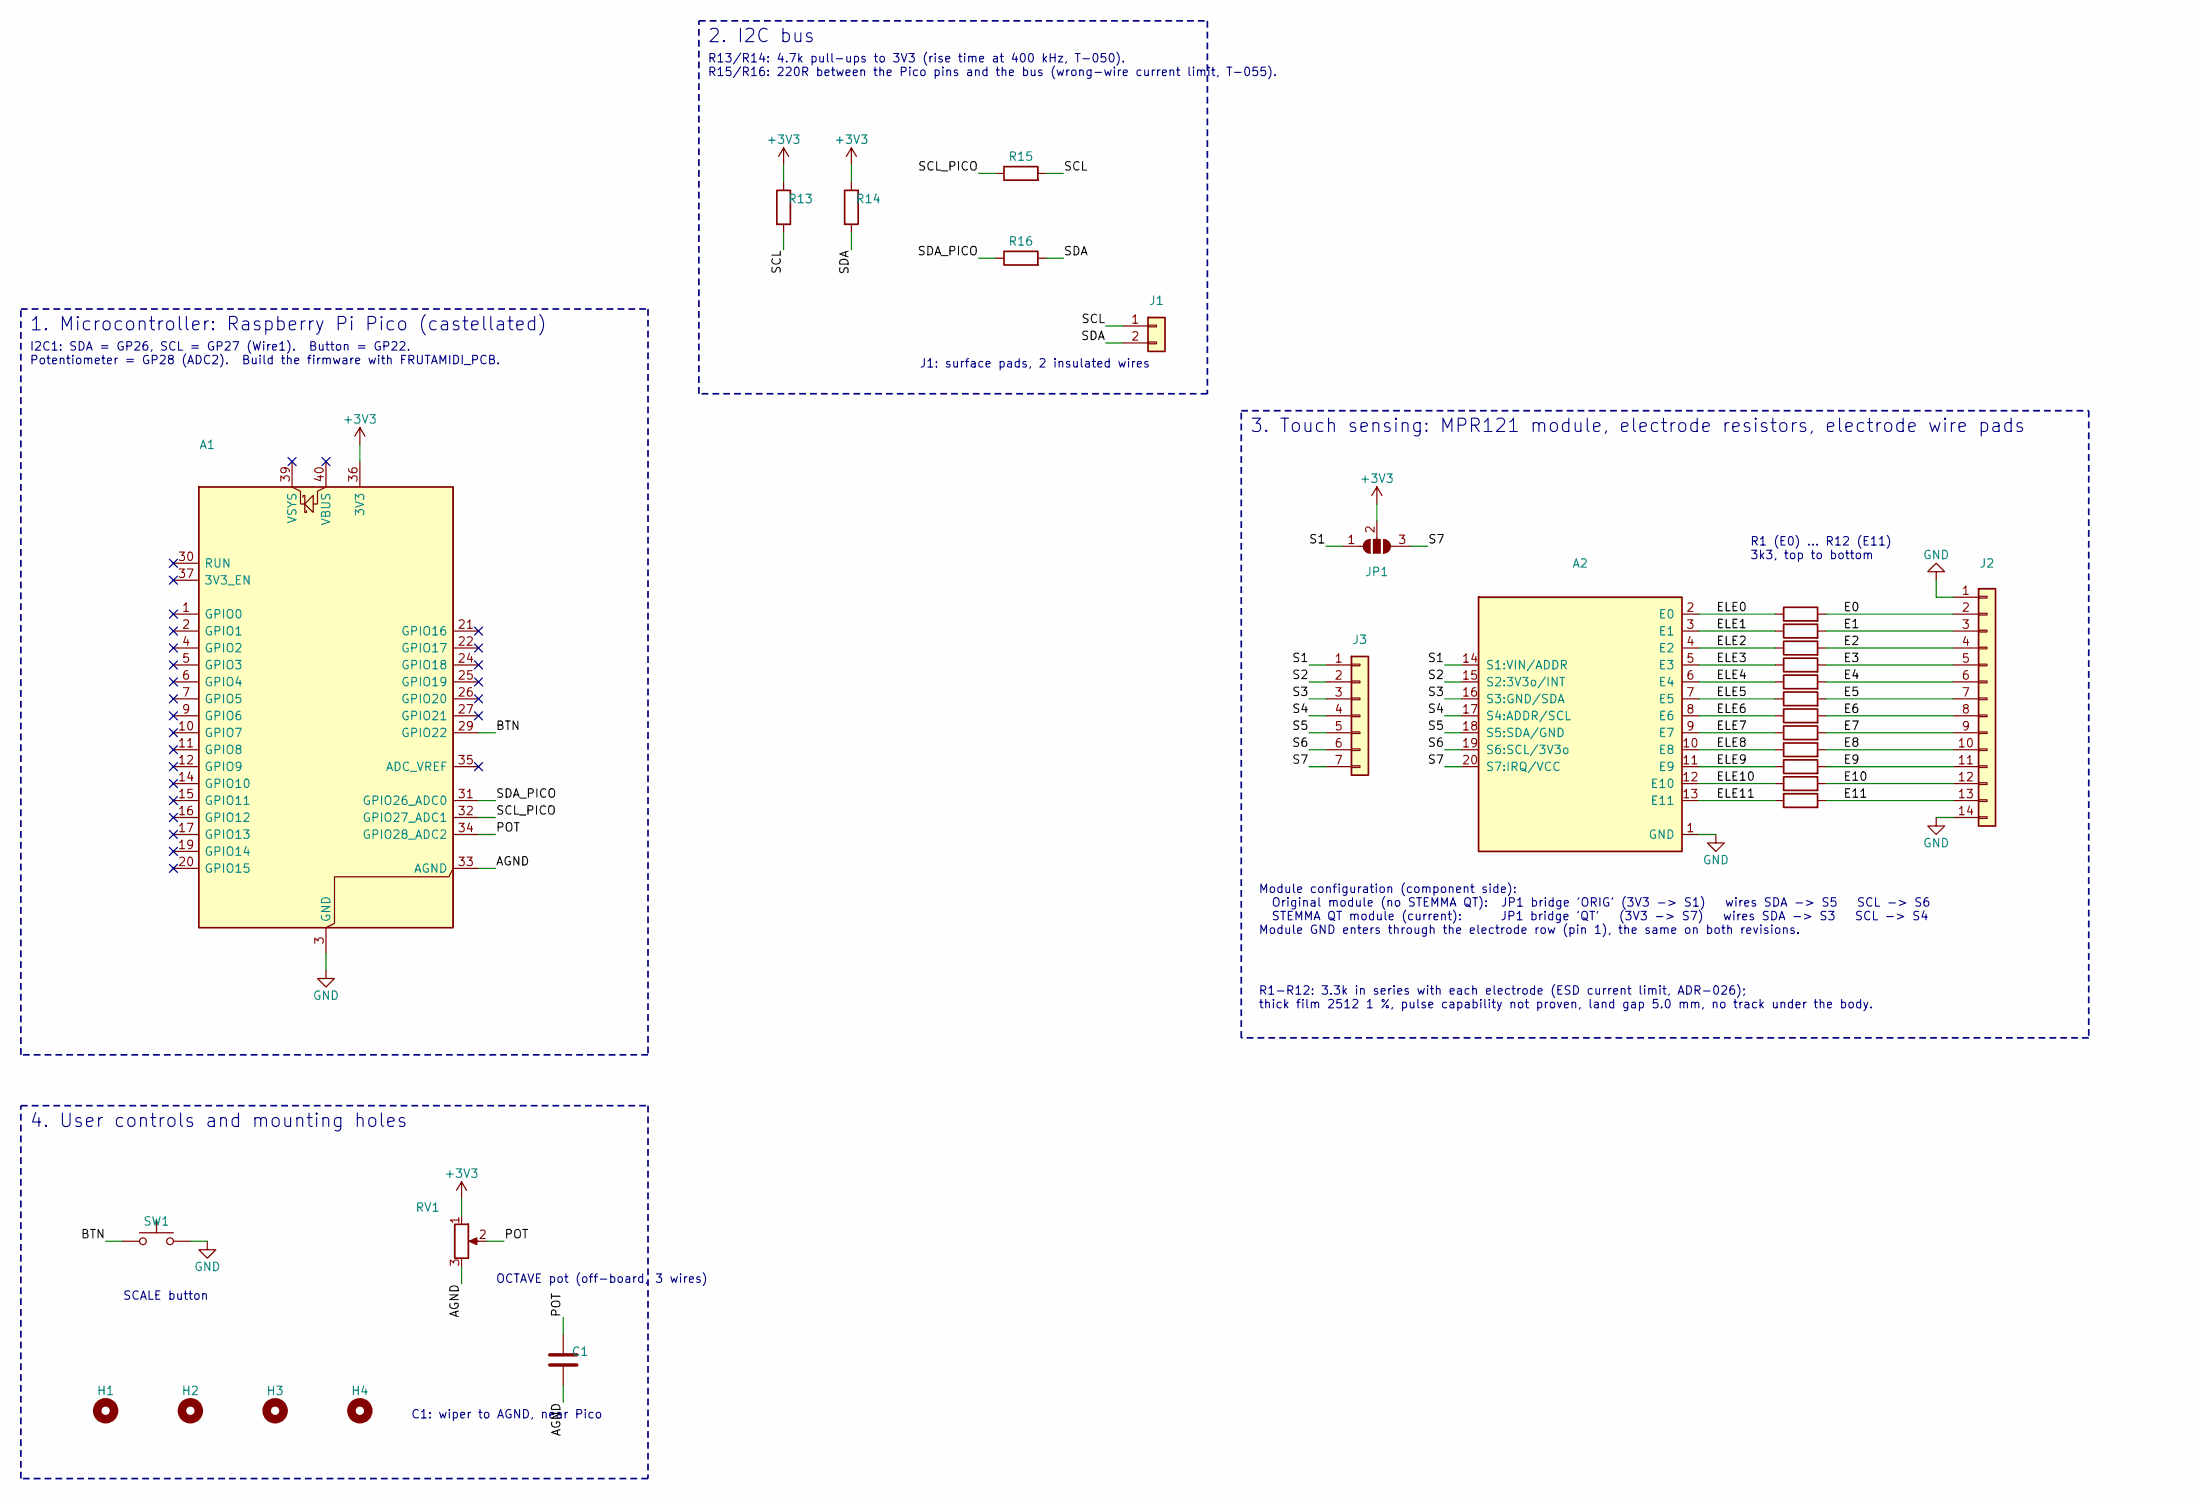
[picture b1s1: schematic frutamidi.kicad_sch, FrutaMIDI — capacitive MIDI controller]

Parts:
A1: RaspberryPi_Pico; RaspberryPi_Pico_Castellated_HomeEtch; MPN SC0915; Mouser 358-SC0915
A2: Adafruit_MPR121_1982; Adafruit_MPR121_1982_SMD; MPN 1982; Mouser 485-1982
C1: 100n X7R 50V; C_1206_HomeEtch; MPN CL31B104KBCNNNC; Mouser 187-CL31B104KBCNNNC
H1, H2, H3, H4: M3; MountingHole_3.2mm_M3
J1: CFG_SCL_SDA; Config_2pads_SMD
J2: Electrode wire pads 5.08 mm; WirePads_1x14_P5.08mm
J3: WIRE_PADS_S1_S7; WirePads_1x07_P2.54mm
JP1: 3V3_ORIG_QT; SolderJumper_3_SMD_P3.81mm
R1, R2, R3, R4, R5, R6, R7, R8, R9, R10, R11, R12: 3k3; R_2512_HomeEtch_G5.0mm; MPN RC2512FK-073K3L; Mouser 603-RC2512FK-073K3L
R13, R14: 4k7; R_1206_HomeEtch; MPN RC1206FR-074K7L; Mouser 603-RC1206FR-074K7L
R15, R16: 220; R_1206_HomeEtch; MPN RC1206FR-07220RL; Mouser 603-RC1206FR-07220RL
RV1: 10k lin (B10K); WirePads_1x03_P5.08mm; MPN PTV09A-4015F-B103; Mouser 652-PTV09A-4015FB103
SW1: B3S-1000; SW_SPST_B3S-1000_HomeEtch; MPN B3S-1000; Mouser 653-B3S-1000

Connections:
+3V3: A1.36 (3V3), JP1.2 (C), R13.1, R14.1, RV1.1
/AGND: A1.33 (AGND), C1.2, RV1.3
/BTN: A1.29 (GPIO22), SW1.1
/E0: J2.2, R1.2
/E1: J2.3, R2.2
/E2: J2.4, R3.2
/E3: J2.5, R4.2
/E4: J2.6, R5.2
/E5: J2.7, R6.2
/E6: J2.8, R7.2
/E7: J2.9, R8.2
/E8: J2.10, R9.2
/E9: J2.11, R10.2
/E10: J2.12, R11.2
/E11: J2.13, R12.2
/ELE0: A2.2 (E0), R1.1
/ELE1: A2.3 (E1), R2.1
/ELE2: A2.4 (E2), R3.1
/ELE3: A2.5 (E3), R4.1
/ELE4: A2.6 (E4), R5.1
/ELE5: A2.7 (E5), R6.1
/ELE6: A2.8 (E6), R7.1
/ELE7: A2.9 (E7), R8.1
/ELE8: A2.10 (E8), R9.1
/ELE9: A2.11 (E9), R10.1
/ELE10: A2.12 (E10), R11.1
/ELE11: A2.13 (E11), R12.1
/POT: A1.34 (GPIO28_ADC2), C1.1, RV1.2
/S1: A2.14 (S1:VIN/ADDR), J3.1, JP1.1 (A)
/S2: A2.15 (S2:3V3o/INT), J3.2
/S3: A2.16 (S3:GND/SDA), J3.3
/S4: A2.17 (S4:ADDR/SCL), J3.4
/S5: A2.18 (S5:SDA/GND), J3.5
/S6: A2.19 (S6:SCL/3V3o), J3.6
/S7: A2.20 (S7:IRQ/VCC), J3.7, JP1.3 (B)
/SCL: J1.1, R13.2, R15.2
/SCL_PICO: A1.32 (GPIO27_ADC1), R15.1
/SDA: J1.2, R14.2, R16.2
/SDA_PICO: A1.31 (GPIO26_ADC0), R16.1
GND: A1.3 (GND), A1.8 (GND), A1.13 (GND), A1.18 (GND), A1.23 (GND), A1.28 (GND), A1.38 (GND), A2.1 (GND), J2.1, J2.14, SW1.2

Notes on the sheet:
1. Microcontroller: Raspberry Pi Pico (castellated)
I2C1: SDA = GP26, SCL = GP27 (Wire1). Button = GP22. Potentiometer = GP28 (ADC2). Build the firmware with FRUTAMIDI_PCB.
2. I2C bus
R13/R14: 4.7k pull-ups to 3V3 (rise time at 400 kHz, T-050). R15/R16: 220R between the Pico pins and the bus (wrong-wire current limit, T-055).
J1: surface pads, 2 insulated wires
3. Touch sensing: MPR121 module, electrode resistors, electrode wire pads
R1 (E0) ... R12 (E11) 3k3, top to bottom
Module configuration (component side): Original module (no STEMMA QT): JP1 bridge 'ORIG' (3V3 -> S1) wires SDA -> S5 SCL -> S6 STEMMA QT module (current): JP1 bridge 'QT' (3V3 -> S7) wires SDA -> S3 SCL -> S4 Module GND enters through the electrode row (pin 1), the same on both revisions.
R1-R12: 3.3k in series with each electrode (ESD current limit, ADR-026); thick film 2512 1 %, pulse capability not proven, land gap 5.0 mm, no track under the body.
4. User controls and mounting holes
SCALE button
OCTAVE pot (off-board, 3 wires)
C1: wiper to AGND, near Pico

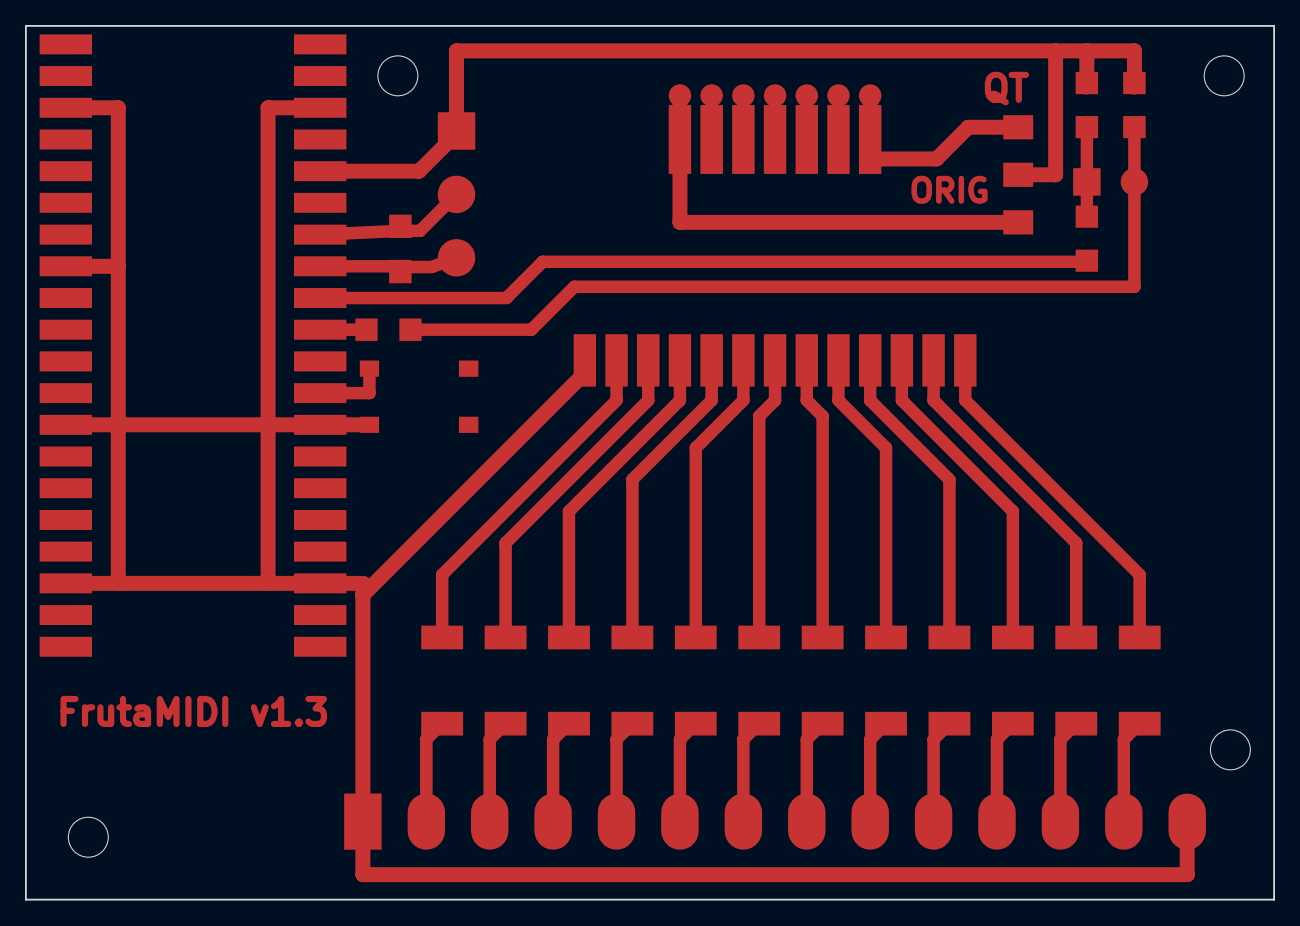
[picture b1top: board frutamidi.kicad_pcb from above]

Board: 2 copper layers, 100.0 x 70.0 mm, 29 parts (0 on the bottom side), 40 nets.

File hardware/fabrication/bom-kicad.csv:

"Ref","Value","Footprint","Manufacturer","MPN","Mouser","Qty"
"A1","RaspberryPi_Pico","FrutaMIDI:RaspberryPi_Pico_Castellated_HomeEtch","Raspberry Pi","SC0915","358-SC0915","1"
"A2","Adafruit_MPR121_1982","FrutaMIDI:Adafruit_MPR121_1982_SMD","Adafruit","1982","485-1982","1"
"C1","100n X7R 50V","FrutaMIDI:C_1206_HomeEtch","Samsung","CL31B104KBCNNNC","187-CL31B104KBCNNNC","1"
"R1-R12","3k3","FrutaMIDI:R_2512_HomeEtch_G5.0mm","YAGEO","RC2512FK-073K3L","603-RC2512FK-073K3L","12"
"R13,R14","4k7","FrutaMIDI:R_1206_HomeEtch","YAGEO","RC1206FR-074K7L","603-RC1206FR-074K7L","2"
"R15,R16","220","FrutaMIDI:R_1206_HomeEtch","YAGEO","RC1206FR-07220RL","603-RC1206FR-07220RL","2"
"RV1","10k lin (B10K)","FrutaMIDI:WirePads_1x03_P5.08mm","Bourns","PTV09A-4015F-B103","652-PTV09A-4015FB103","1"
"SW1","B3S-1000","FrutaMIDI:SW_SPST_B3S-1000_HomeEtch","Omron","B3S-1000","653-B3S-1000","1"

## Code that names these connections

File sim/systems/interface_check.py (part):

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  - Adafruit 1982 header nets for both revisions (SOURCE: Adafruit Eagle files, see
    requirements/SOURCES_SYSTEMS.md S-06/S-07) and the 180-degree footprint rotation in gen_pcb.py
  - README.md / hardware/README.md pin tables
T-093 (CR-003, ADR-023): adapted to the v1.3 SMD board: footprints, MPNs, pad types, label, AGND without RV1 tabs, BOM file, manual.
T-099 (ADR-024 BOM at Mouser, ADR-026 R1-R12 YAGEO RC2512FK-073K3L 3k3, T-098 footprint R_2512_HomeEtch_G5.0mm, RV1 Bourns PTV09A).
Prints one line per check: PASS / FAIL, and a final summary line.
Usage: python3 sim/systems/interface_check.py [board.kicad_pcb [hardware_README.md [MANUAL.md [bom.csv [README.md]]]]]   (scratch copies for mutation tests)
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    check("fw.%s.i2c_instance" % v, ok, "%s SDA=GP%d SCL=GP%d" % (bus, sda, scl))

# Firmware PCB pins vs PCB nets on the Pico socket A1
pcb_expect = {"PIN_SDA": "SDA", "PIN_SCL": "SCL", "PIN_BUTTON": "BTN", "PIN_POT": "POT"}
for const, net in pcb_expect.items():
    gp = "GP%d" % fw["pcb"][const]
    phys = GP_TO_PHYS[gp]
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used = {str(GP_TO_PHYS["GP%d" % fw["pcb"][c]]) for c in pcb_expect} | {"36", "33"} | {str(n) for n in gnd_pads}
others = {p: n for p, n in fps["A1"].items() if p not in used and n != {None} and not any(x and x.startswith("unconnected") for x in n)}
check("pcb.A1.no_other_nets", not others, "other connected pads: %s" % others)
# AGND membership rule (T-077, ADR-021; ADR-023 removes the RV1 tabs): AGND joins exactly A1 pin 33, RV1 pin 3 (off-board
# pot wire pad) and C1 pin 2 (wiper filter to AGND); nothing else. The off-board pot has no board-side mounting tab. It relies on the Pico-internal AGND-GND link (S-02 'also a GND pin';
# S-01 sec. 2.1 'separate analog ground plane ... terminating at this pin'), so no other AGND-GND join may exist.
AGND_ALLOWED = {("A1", "33"), ("RV1", "3"), ("C1", "2")}
agnd_members = sorted({(r, p) for r, f in fps.items() for p, n in f.items() if "AGND" in n})
check("pcb.AGND_membership", set(agnd_members) == AGND_ALLOWED,
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check("pcb.RV1_offboard_3_pads", sorted(fps["RV1"]) == ["1", "2", "3"] and all(PAD_TYPES["RV1"][n] == {"smd"} for n in "123"),
      "RV1 pads %s, types %s (ADR-023 D-2: off-board pot on 3 wire pads, no mounting tabs on the board)" % (sorted(fps["RV1"]), PAD_TYPES["RV1"]))
c1 = fps.get("C1", {})
check("pcb.C1_wiper_filter", [c1.get(n) for n in "12"] == [{"POT"}, {"AGND"}] and len(c1) == 2
      and VALUES.get("C1", "").startswith("100n"),
      "C1 1/2 = %s, value %r (ADR-021: 100 nF POT to AGND; ADR-023: 1206)" % ([c1.get(n) for n in "12"], VALUES.get("C1")))
pot_members = sorted((r, p) for r, f in fps.items() for p, n in f.items() if "POT" in n)
check("pcb.POT_membership", set(pot_members) == {("A1", str(GP_TO_PHYS["GP%d" % fw["pcb"]["PIN_POT"]])), ("RV1", "2"), ("C1", "1")},
      "POT pads %s" % pot_members)
sw = set().union(*fps["SW1"].values())
check("pcb.SW1", sw == {"BTN", "GND"}, "SW1 nets %s (active low, firmware INPUT_PULLUP)" % sorted(sw))
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    ok = re.search(r"\| %s[^|]*\| %d \|" % (gp, phys), txt) is not None and GP_TO_PHYS[gp] == phys
    check("doc.%s.%s" % (src, gp), ok, "%s at physical pin %d" % (gp, phys))
bb = fw["breadboard"]
check("doc.README_vs_fw_breadboard", (bb["PIN_SDA"], bb["PIN_SCL"], bb["PIN_BUTTON"], bb["PIN_POT"]) == (4, 5, 15, 26),
      "firmware breadboard SDA/SCL/BTN/POT = GP%d/GP%d/GP%d/GP%d, README GP4/GP5/GP15/GP26"
      % (bb["PIN_SDA"], bb["PIN_SCL"], bb["PIN_BUTTON"], bb["PIN_POT"]))
for sig, phys, gp in (("SDA", 31, "GP26"), ("SCL", 32, "GP27"), ("Button", 29, "GP22"), ("Potentiometer", 34, "GP28")):
    ok = re.search(r"\| %s[^|]*\| %d \| %s" % (sig, phys, gp), hw_readme) is not None
    check("doc.hw_readme.%s" % sig, ok and GP_TO_PHYS[gp] == phys, "%s pin %d %s" % (sig, phys, gp))
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

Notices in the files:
hardware/README.md:
The module footprint was measured from [Adafruit's Eagle files](https://github.com/adafruit/Adafruit-MPR121-PCB) (CC BY-SA). Both versions have the same geometry: only the order of the 7-pin row changes.
